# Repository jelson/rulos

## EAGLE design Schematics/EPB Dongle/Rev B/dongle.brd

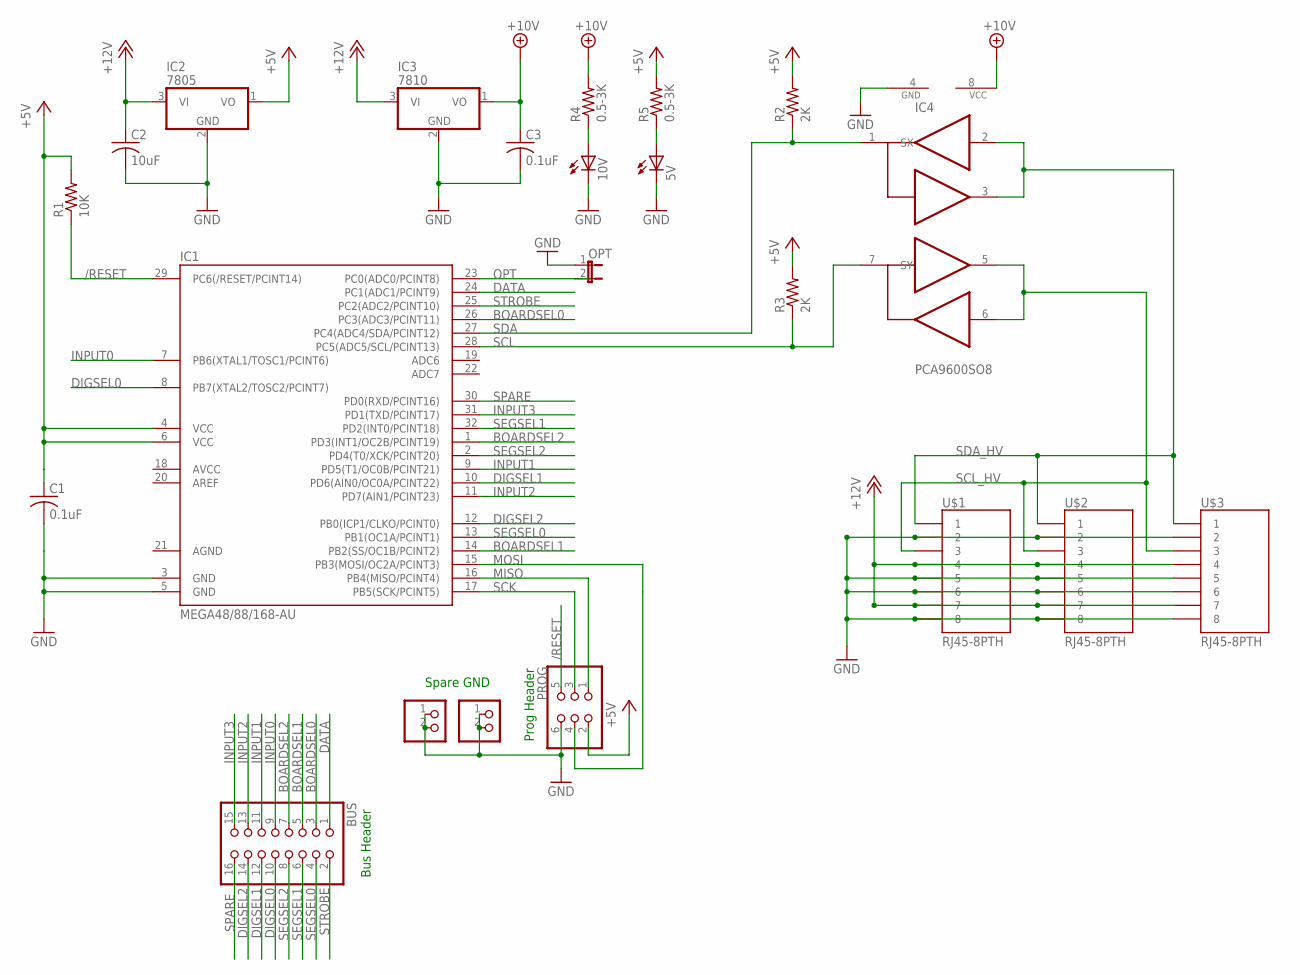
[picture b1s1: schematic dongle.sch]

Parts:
5V, 10V: LED3MM
BUS: PINHD-2X8; 2X08
C1, C3: 0.1uF; C025-025X050
C2: 10uF; C025-025X050
GROUND1, GROUND2: PINHD-1X2; 1X02
IC1: MEGA48/88/168-AU; TQFP32-08
IC2: 7805; TO92
IC3: 7810; TO92
IC4: PCA9600SO8; SO08
OPT: JUMPER-2PTH; 1X02
PROG: PINHD-2X3; 2X03
R1: 10K; 0204/5
R2, R3: 2K; 0204/5
R4, R5: 0.5-3K; 0204/5
U$1, U$2, U$3: RJ45-8PTH; RJ45-8

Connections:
+5V: C1.1, IC1.4 (VCC), IC1.6 (VCC), IC2.1 (VO), PROG.2, R1.2, R2.2, R3.2, R5.2
+10V: C3.1, IC3.1 (VO), IC4.8 (VCC), R4.2
+12V: C2.1, IC2.3 (VI), IC3.3 (VI), U$1.4, U$1.7, U$2.4, U$2.7, U$3.4, U$3.7
/RESET: IC1.29 (PC6(/RESET/PCINT14)), PROG.5, R1.1
AGND: IC1.21 (AGND)
BOARDSEL0: BUS.3, IC1.26 (PC3(ADC3/PCINT11))
BOARDSEL1: BUS.5, IC1.14 (PB2(SS/OC1B/PCINT2))
BOARDSEL2: BUS.7, IC1.1 (PD3(INT1/OC2B/PCINT19))
DATA: BUS.1, IC1.24 (PC1(ADC1/PCINT9))
DIGSEL0: BUS.10, IC1.8 (PB7(XTAL2/TOSC2/PCINT7))
DIGSEL1: BUS.12, IC1.10 (PD6(AIN0/OC0A/PCINT22))
DIGSEL2: BUS.14, IC1.12 (PB0(ICP1/CLKO/PCINT0))
GND: 5V.K (C), 10V.K (C), C1.2, C2.2, C3.2, GROUND1.1, GROUND1.2, GROUND2.1, GROUND2.2, IC1.3 (GND), IC1.5 (GND), IC2.2 (GND), IC3.2 (GND), IC4.4 (GND), OPT.1, PROG.6, U$1.2, U$1.5, U$1.6, U$1.8, U$2.2, U$2.5, U$2.6, U$2.8, U$3.2, U$3.5, U$3.6, U$3.8
INPUT0: BUS.9, IC1.7 (PB6(XTAL1/TOSC1/PCINT6))
INPUT1: BUS.11, IC1.9 (PD5(T1/OC0B/PCINT21))
INPUT2: BUS.13, IC1.11 (PD7(AIN1/PCINT23))
INPUT3: BUS.15, IC1.31 (PD1(TXD/PCINT17))
MISO: IC1.16 (PB4(MISO/PCINT4)), PROG.1
MOSI: IC1.15 (PB3(MOSI/OC2A/PCINT3)), PROG.4
unnamed: 5V.A, R5.1
unnamed: 10V.A, R4.1
OPT: IC1.23 (PC0(ADC0/PCINT8)), OPT.2
SCK: IC1.17 (PB5(SCK/PCINT5)), PROG.3
SCL: IC1.28 (PC5(ADC5/SCL/PCINT13)), IC4.7 (SY), R3.1
SCL_HV: IC4.5 (TY), IC4.6 (RY), U$1.3, U$2.3, U$3.3
SDA: IC1.27 (PC4(ADC4/SDA/PCINT12)), IC4.1 (SX), R2.1
SDA_HV: IC4.2 (RX), IC4.3 (TX), U$1.1, U$2.1, U$3.1
SEGSEL0: BUS.4, IC1.13 (PB1(OC1A/PCINT1))
SEGSEL1: BUS.6, IC1.32 (PD2(INT0/PCINT18))
SEGSEL2: BUS.8, IC1.2 (PD4(T0/XCK/PCINT20))
SPARE: BUS.16, IC1.30 (PD0(RXD/PCINT16))
STROBE: BUS.2, IC1.25 (PC2(ADC2/PCINT10))

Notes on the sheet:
Bus Header
Prog Header
Spare GND

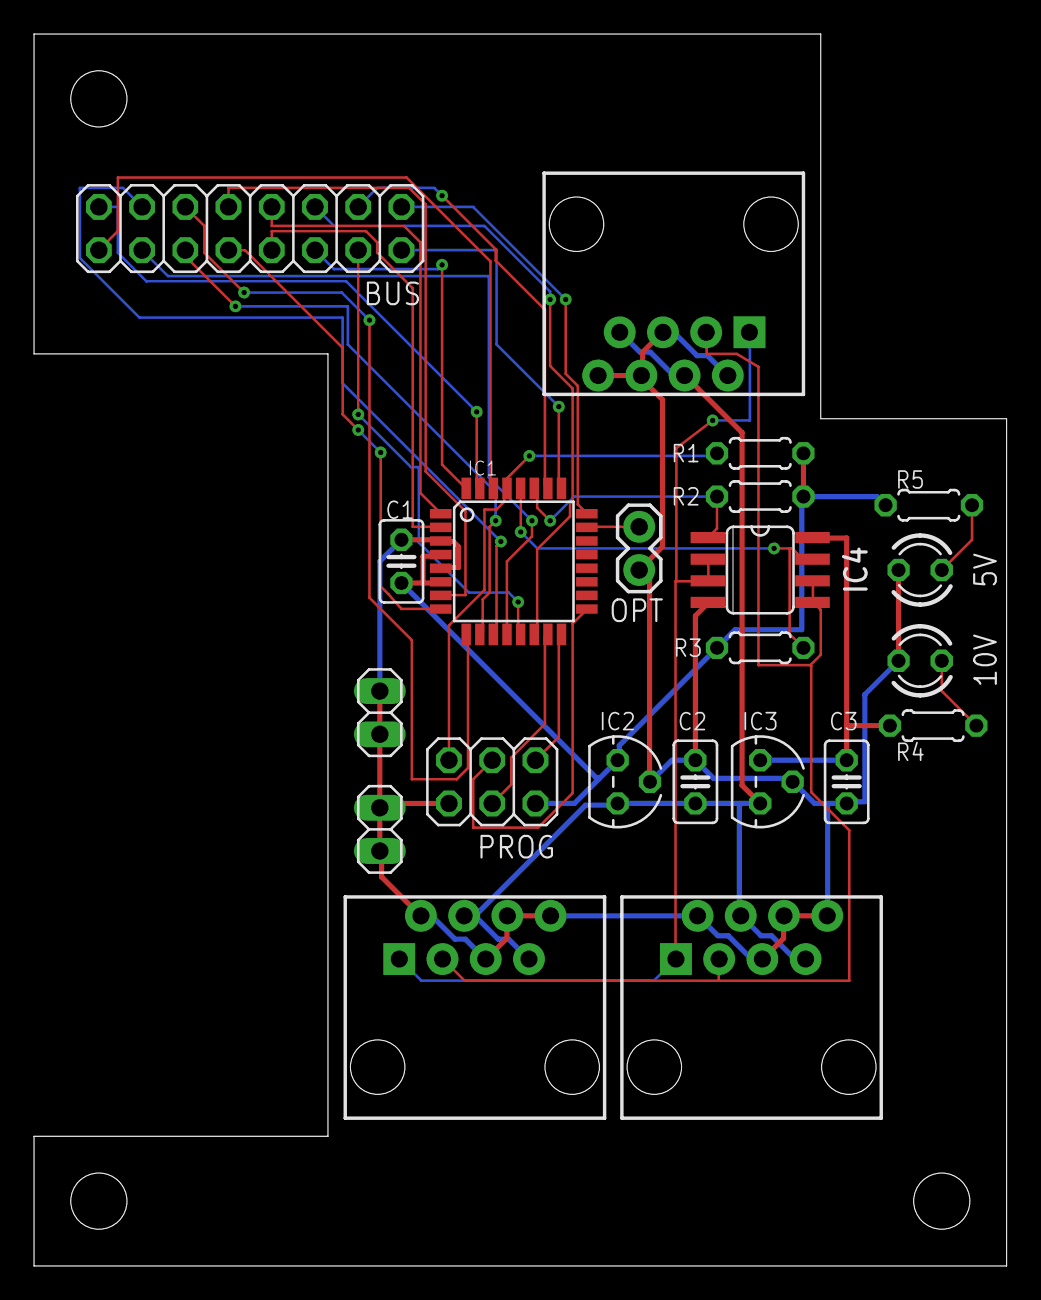
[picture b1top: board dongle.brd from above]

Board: 2 copper layers, 57.1 x 72.4 mm, 25 parts (0 on the bottom side), 31 nets.

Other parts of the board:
U$5, U$6, U$7: STAND-OFF

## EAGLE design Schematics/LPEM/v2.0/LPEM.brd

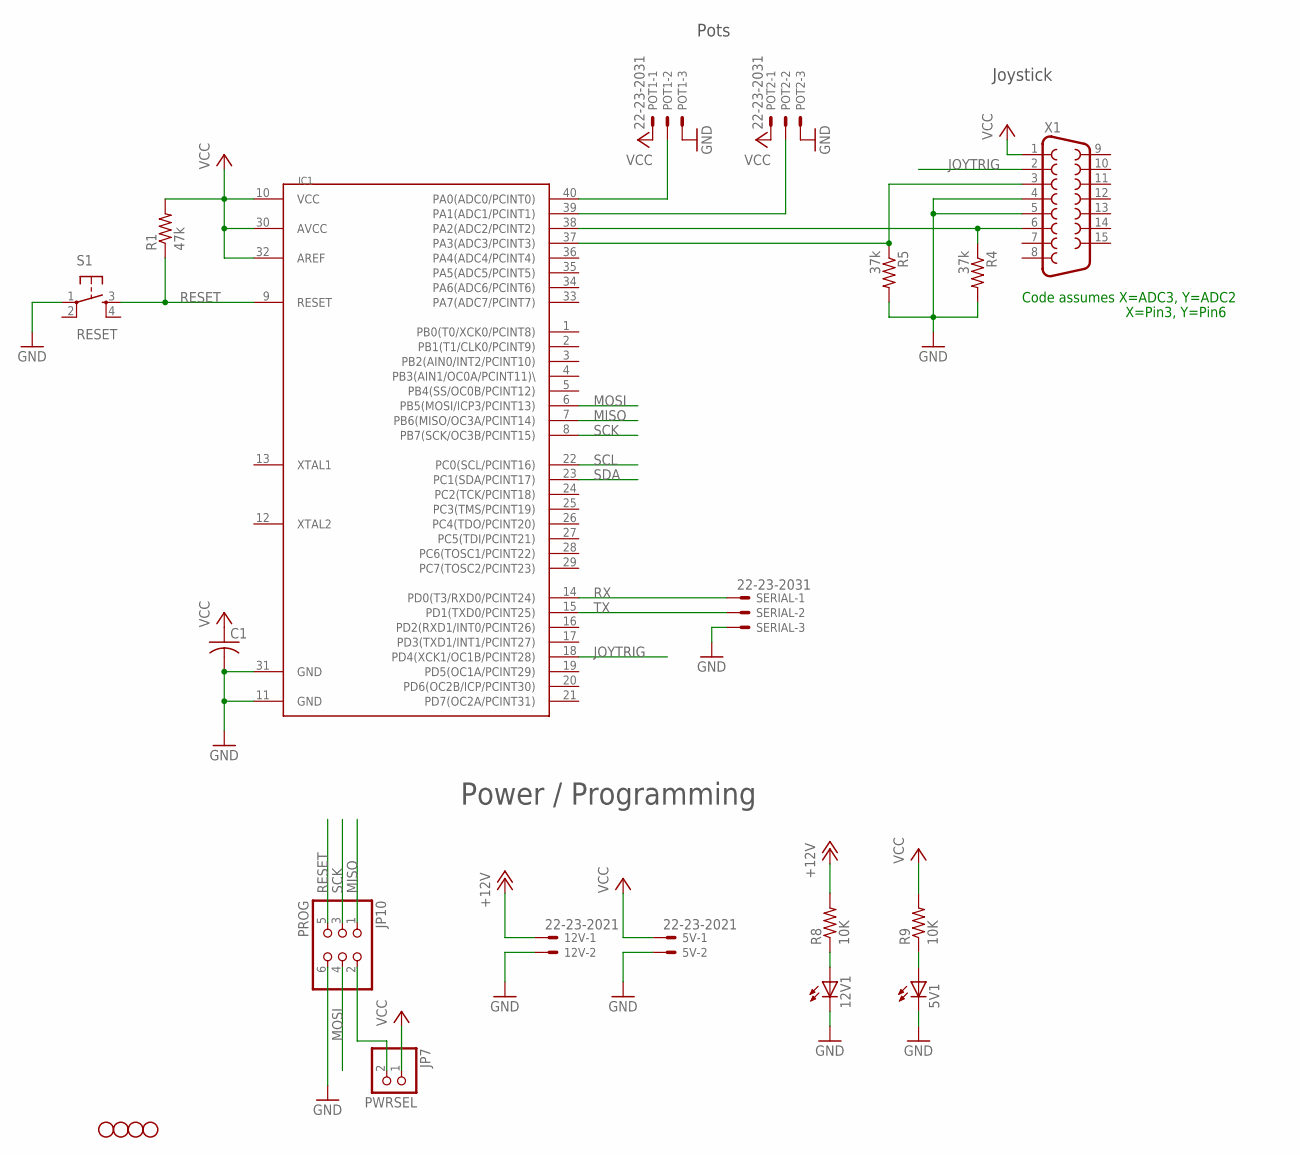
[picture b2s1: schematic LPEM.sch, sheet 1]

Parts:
5V, 12V: 22-23-2021
5V1, 12V1: LED3MM
C1: C-US025-025X050; C025-025X050
IC1: MEGA1284P; DIL40
JP1, JP2, JP8, JP9: STAND-OFF
JP7: PWRSEL; 1X02
JP10: PROG; 2X03
POT1, POT2: 22-23-2031
R1: 47k; 0204/5
R4, R5: 37k; 0204/5
R8, R9: 10K; 0204/5
S1: RESET; TACTILE-PTH
SERIAL: 22-23-2031
X1: F15HP

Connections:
+12V: 12V.1, R8.2; also elsewhere on the board
GND: 5V.2, 5V1.K (C), 12V.2, 12V1.K (C), C1.2, IC1.11 (GND), IC1.31 (GND), JP10.6, POT1.3, POT2.3, R4.2, R5.2, S1.1, SERIAL.3, X1.4, X1.5; also elsewhere on the board
JOYTRIG: IC1.18 (PD4(XCK1/OC1B/PCINT28)), X1.2
MISO: IC1.7 (PB6(MISO/OC3A/PCINT14)), JP10.1
MOSI: IC1.6 (PB5(MOSI/ICP3/PCINT13)), JP10.4
unnamed: IC1.40 (PA0(ADC0/PCINT0)), POT1.2
unnamed: IC1.39 (PA1(ADC1/PCINT1)), POT2.2
unnamed: IC1.37 (PA3(ADC3/PCINT3)), R5.1, X1.3
unnamed: JP7.2, JP10.2
unnamed: 5V1.A, R9.1
unnamed: IC1.38 (PA2(ADC2/PCINT2)), R4.1, X1.6
unnamed: 12V1.A, R8.1
RESET: IC1.9 (RESET), JP10.5, R1.1, S1.3
RX: IC1.14 (PD0(T3/RXD0/PCINT24)), SERIAL.1
SCK: IC1.8 (PB7(SCK/OC3B/PCINT15)), JP10.3
SCL: IC1.22 (PC0(SCL/PCINT16)); also elsewhere on the board
SDA: IC1.23 (PC1(SDA/PCINT17)); also elsewhere on the board
TX: IC1.15 (PD1(TXD0/PCINT25)), SERIAL.2
VCC: 5V.1, C1.1, IC1.10 (VCC), IC1.30 (AVCC), IC1.32 (AREF), JP7.1, POT1.1, POT2.1, R1.2, R9.2, X1.1; also elsewhere on the board

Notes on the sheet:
Code assumes X=ADC3, Y=ADC2
X=Pin3, Y=Pin6
Power / Programming
Joystick
Pots

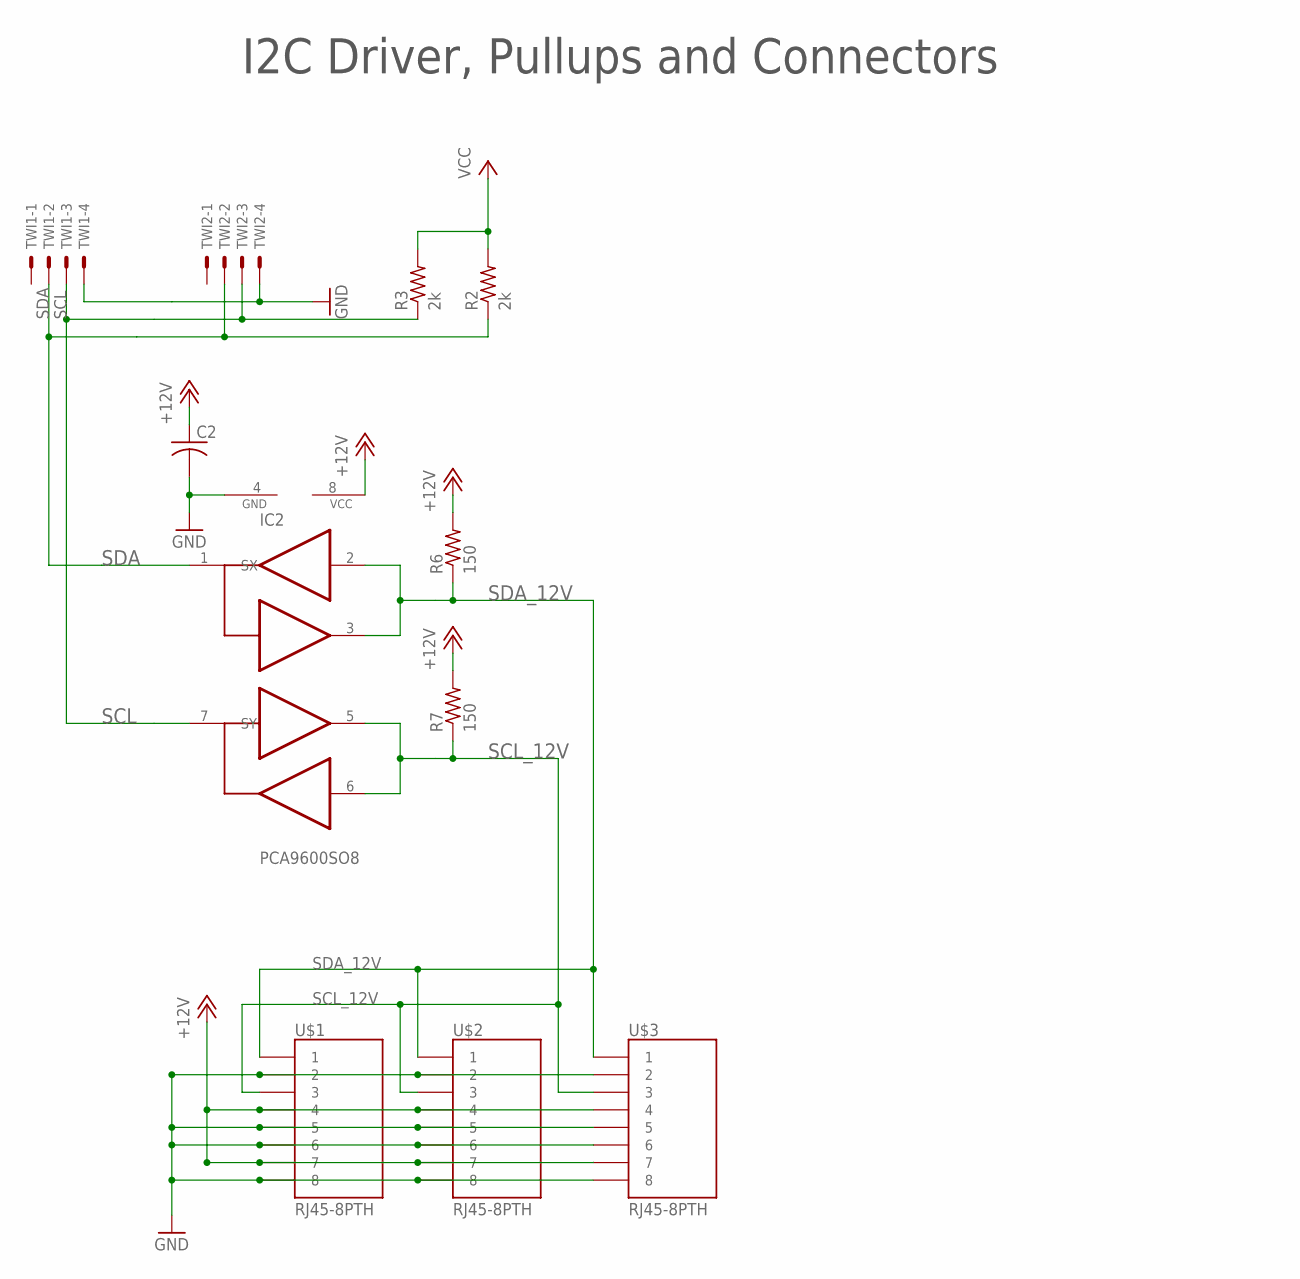
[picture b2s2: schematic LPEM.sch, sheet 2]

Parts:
C2: C-US025-025X050; C025-025X050
IC2: PCA9600SO8; SO08
R2, R3: 2k; 0204/5
R6, R7: 150; 0204/5
TWI1, TWI2: 22-23-2041
U$1, U$2, U$3: RJ45-8PTH; RJ45-8

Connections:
+12V: C2.1, IC2.8 (VCC), R6.2, R7.2, U$1.4, U$1.7, U$2.4, U$2.7, U$3.4, U$3.7; also elsewhere on the board
GND: C2.2, IC2.4 (GND), TWI1.4, TWI2.4, U$1.2, U$1.5, U$1.6, U$1.8, U$2.2, U$2.5, U$2.6, U$2.8, U$3.2, U$3.5, U$3.6, U$3.8; also elsewhere on the board
SCL: IC2.7 (SY), R3.1, TWI1.3, TWI2.3; also elsewhere on the board
SCL_12V: IC2.5 (TY), IC2.6 (RY), R7.1, U$1.3, U$2.3, U$3.3
SDA: IC2.1 (SX), R2.1, TWI1.2, TWI2.2; also elsewhere on the board
SDA_12V: IC2.2 (RX), IC2.3 (TX), R6.1, U$1.1, U$2.1, U$3.1
VCC: R2.2, R3.2; also elsewhere on the board

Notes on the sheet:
I2C Driver, Pullups and Connectors

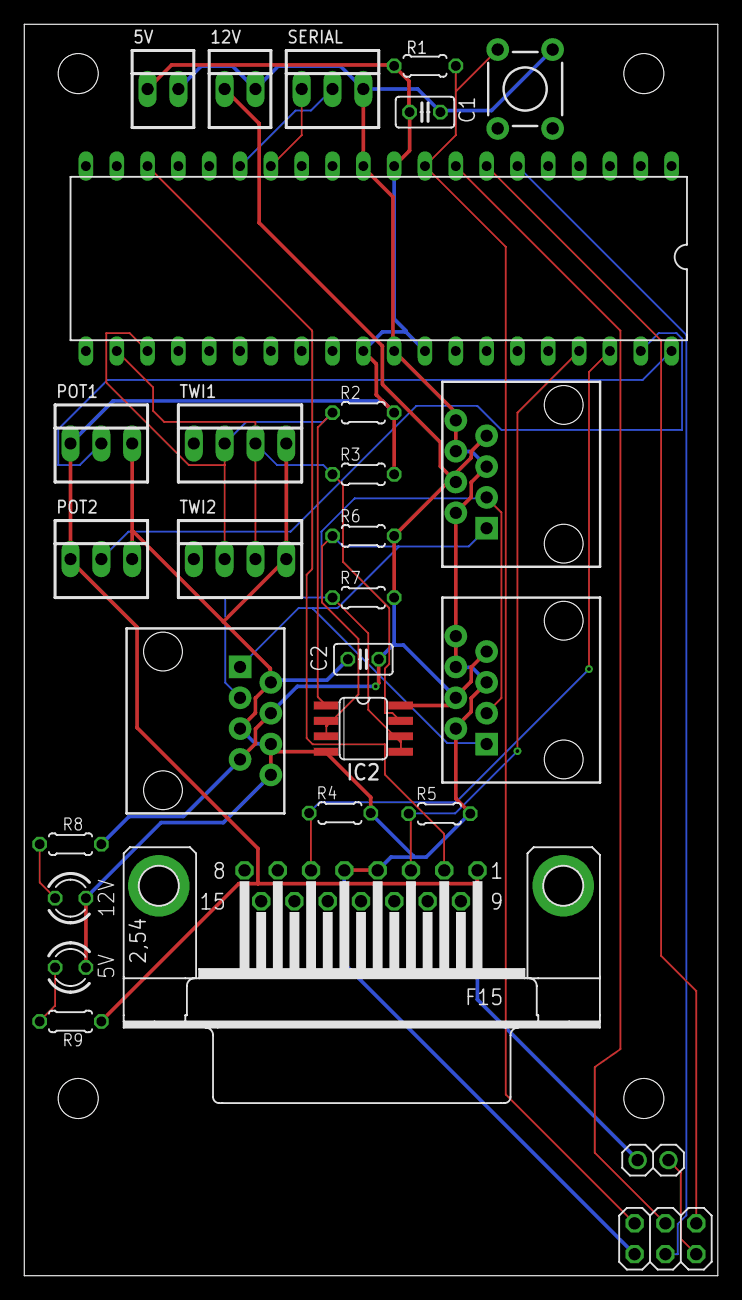
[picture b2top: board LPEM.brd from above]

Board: 2 copper layers, 57.1 x 103.1 mm, 33 parts (0 on the bottom side), 21 nets.

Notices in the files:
parts and their libraries:
SparkFun: Licensing: CC v3.0 Share-Alike You are welcome to use this library for commercial purposes.
